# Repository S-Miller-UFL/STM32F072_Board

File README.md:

This is an STM32F072RBT6 based mcu board.

It contains the following features:
1. An ARM based STM32 microcontroller
2. An FT230 USB to UART transmitter that allows communication between the host computer and the MCU
3. A fully dedicated debug port. Labelled SWD.
4. 4 16 pin ports that are dedicated for communication with other boards. Such as SRAM, or FPGA's.

This design was made using KICAD. It's fully laid out, routed, and ready to be sent off for manufacturing.

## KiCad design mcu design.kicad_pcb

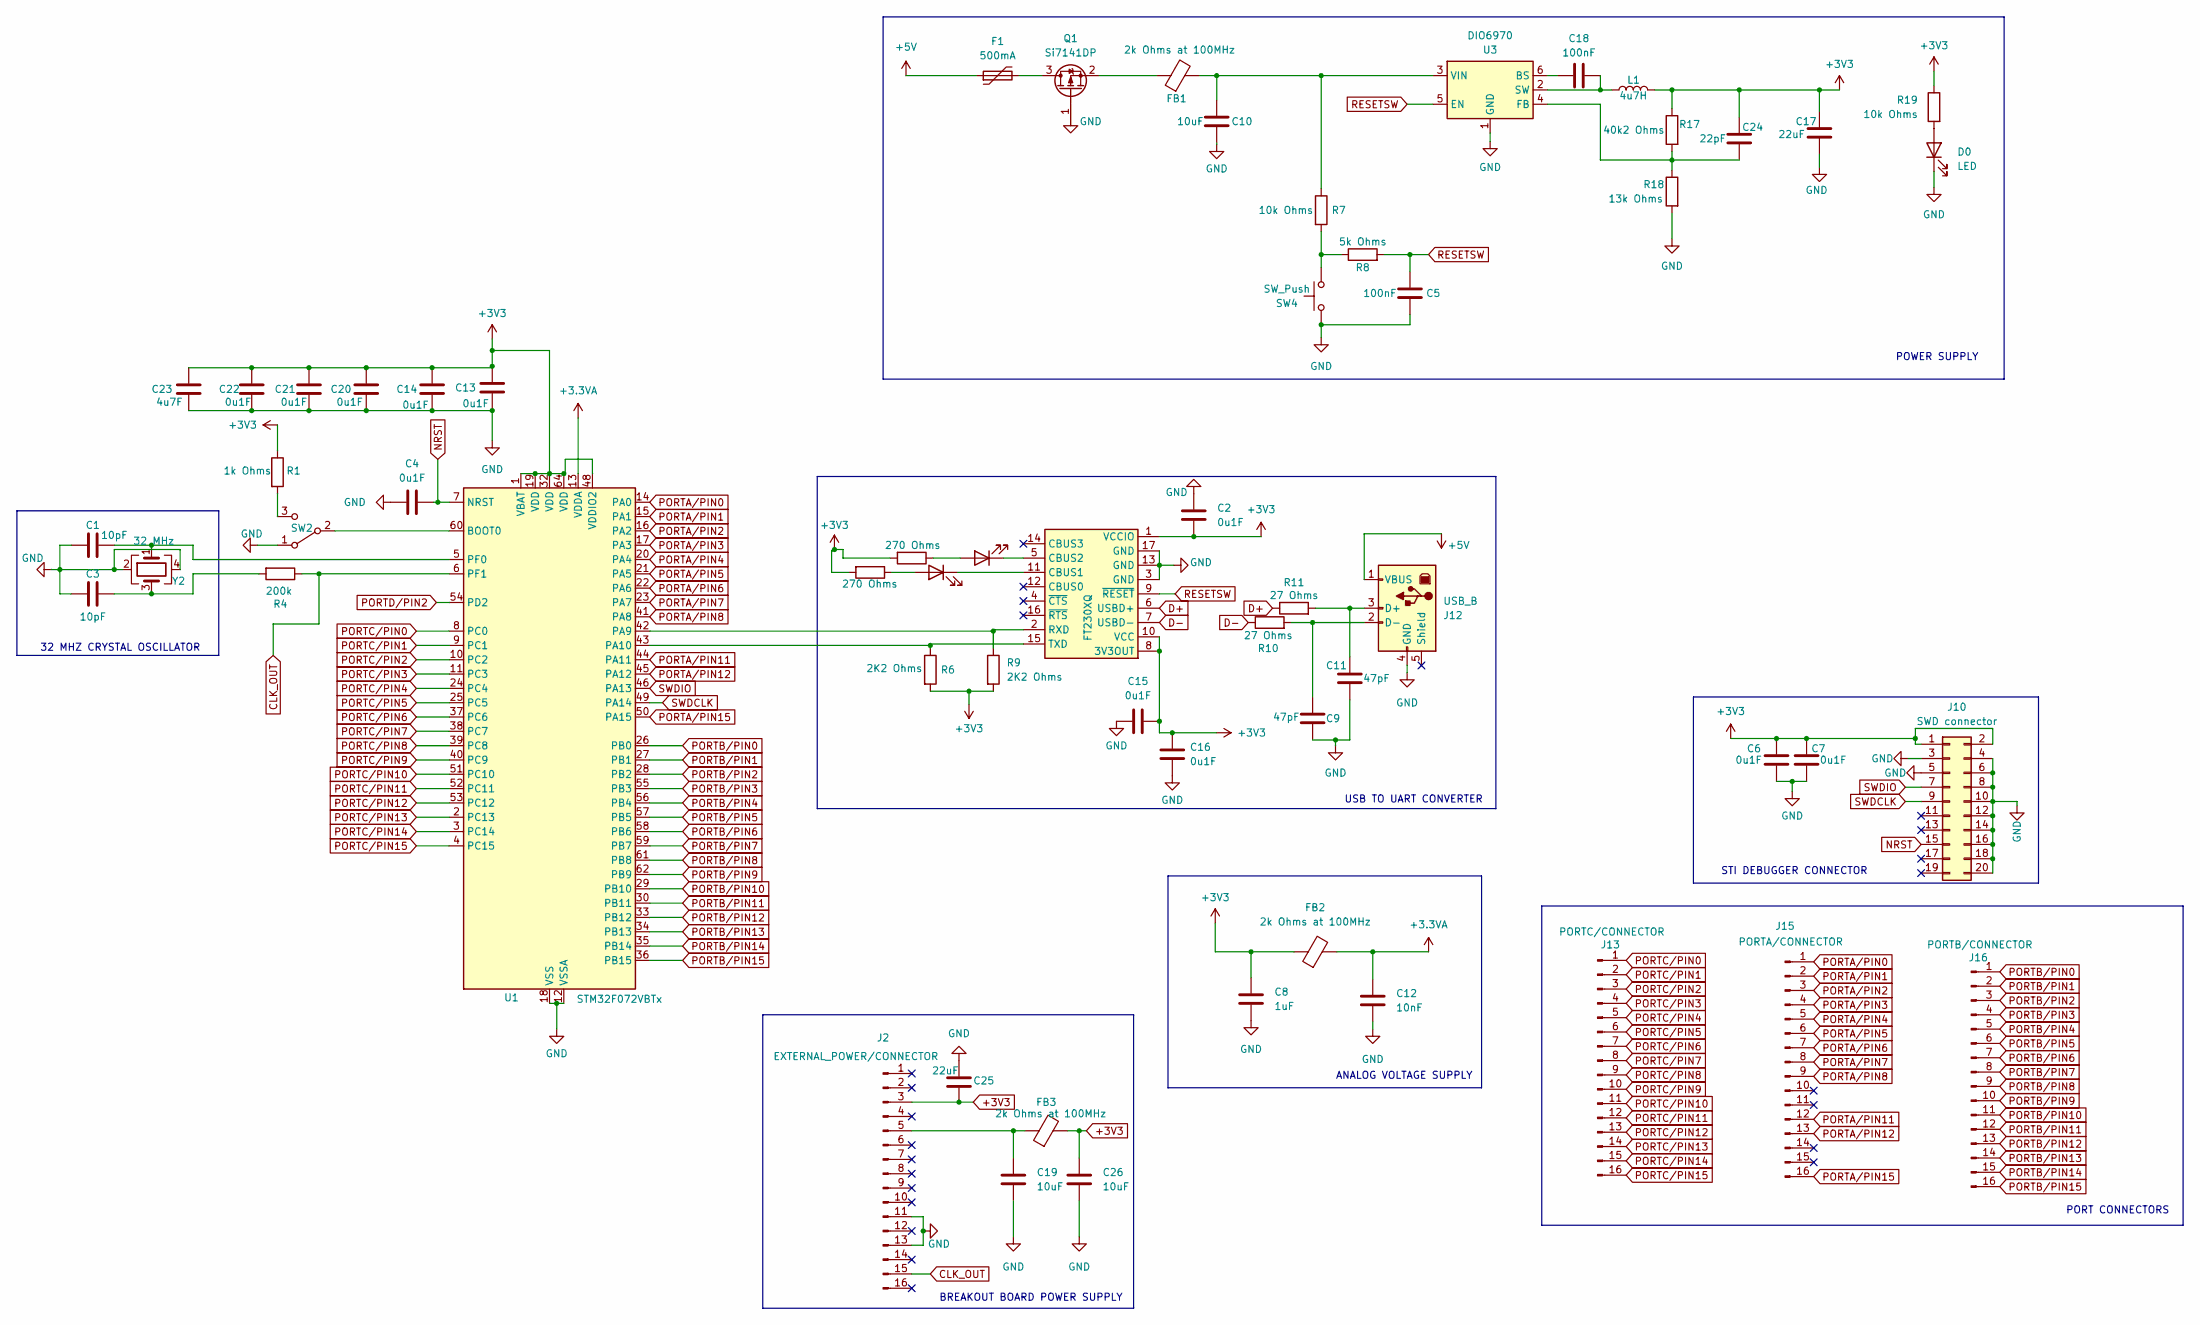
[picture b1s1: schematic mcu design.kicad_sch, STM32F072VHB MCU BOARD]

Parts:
C1, C3: 10pF; C_0402_1005Metric
C2, C4, C6, C7, C13, C14, C15, C16, C20, C21, C22: 0u1F; C_0402_1005Metric
C5, C18: 100nF; C_0402_1005Metric
C8: 1uF; C_0603_1608Metric
C9, C11: 47pF; C_0603_1608Metric
C10, C19, C26: 10uF; C_0603_1608Metric
C12: 10nF; C_0603_1608Metric
C17: 22uF; C_1206_3216Metric
C23: 4u7F; C_0402_1005Metric
C24: 22pF; C_0603_1608Metric
C25: 22uF; C_0402_1005Metric
D0, D1, D2: LED; LED_0603_1608Metric
F1: 500mA; Fuse_1206_3216Metric
FB1, FB2, FB3: 2k Ohms at 100MHz; L_0603_1608Metric
J2: EXTERNAL_POWER/CONNECTOR; PinHeader_1x16_P2.00mm_Vertical
J10: SWD connector; PinHeader_2x10_P2.00mm_Vertical
J12: USB_B; USB_B_Amphenol_MUSB-D511_Vertical_Rugged
J13: PORTC/CONNECTOR; PinHeader_1x16_P2.00mm_Vertical
J15: PORTA/CONNECTOR; PinHeader_1x16_P2.00mm_Vertical
J16: PORTB/CONNECTOR; PinHeader_1x16_P2.00mm_Vertical
L1: 4u7H; L_0805_2012Metric
Q1: Si7141DP; SOT-23
R1: 1k Ohms; R_0402_1005Metric
R2, R3: 270 Ohms; R_0402_1005Metric
R4: 200k; R_0402_1005Metric
R6, R9: 2K2 Ohms; R_0402_1005Metric
R7, R19: 10k Ohms; R_0402_1005Metric
R8: 5k Ohms; R_0402_1005Metric
R10, R11: 27 Ohms; R_0402_1005Metric
R17: 40k2 Ohms; R_0402_1005Metric
R18: 13k Ohms; R_0402_1005Metric
SW2: SW_CuK_JS202011CQN_DPDT_Straight
SW4: SW_Push; SW_Push_1P1T_NO_6x6mm_H9.5mm
U1: STM32F072VBTx; LQFP-64_10x10mm_P0.5mm
U2: FT230XQ; HTSSOP-16-1EP_4.4x5mm_P0.65mm_EP3.4x5mm
U3: DIO6970; SOT-23-6
Y2: 32 MHz; Crystal_SMD_2520-4Pin_2.5x2.0mm

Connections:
+3.3VA: C12.1, FB2.2, U1.13 (VDDA)
+3V3: C2.1, C6.1, C7.1, C8.1, C13.1, C14.1, C15.1, C16.1, C17.2, C20.1, C21.1, C22.1, C23.1, C24.2, C25.2, C26.1, FB2.1, FB3.2, J2.3, J10.1, J10.2, L1.2, R1.1, R2.2, R3.2, R6.2, R9.2, R17.1, R19.1, U1.1 (VBAT), U1.19 (VDD), U1.32 (VDD), U1.48 (VDDIO2), U1.64 (VDD), U2.1 (VCCIO), U2.8 (3V3OUT), U2.10 (VCC)
+5V: F1.1, J12.1 (VBUS)
CLK_OUT: J2.15, R4.1, U1.6 (PF1)
D+: R11.1, U2.6 (USBD+)
D-: R10.1, U2.7 (USBD-)
GND: C1.1, C2.2, C3.1, C4.1, C5.2, C6.2, C7.2, C8.2, C9.2, C10.2, C11.2, C12.2, C13.2, C14.2, C15.2, C16.2, C17.1, C19.2, C20.2, C21.2, C22.2, C23.2, C25.1, C26.2, D0.1 (K), J2.11, J2.13, J10.3, J10.4, J10.5, J10.6, J10.8, J10.10, J10.12, J10.14, J10.16, J10.18, J10.20, J12.4 (GND), Q1.1 (G), R18.2, SW2.1 (A), SW4.2, U1.12 (VSSA), U1.18 (VSS), U1.31 (VSS), U1.47 (VSS), U1.63 (VSS), U2.3 (GND), U2.13 (GND), U2.17 (GND), U3.1 (GND), Y2.2, Y2.4
NRST: C4.2, J10.15, U1.7 (NRST)
unnamed: C3.2, R4.2, Y2.3
unnamed: D0.2 (A), R19.2
unnamed: D1.2 (A), R2.1
unnamed: D1.1 (K), U2.11 (CBUS1)
unnamed: D2.2 (A), R3.1
unnamed: D2.1 (K), U2.5 (CBUS2)
unnamed: C19.1, FB3.1, J2.5
unnamed: C11.1, J12.3 (D+), R11.2
unnamed: C9.1, J12.2 (D-), R10.2
unnamed: F1.2, Q1.3 (D)
unnamed: FB1.1, Q1.2 (S)
unnamed: R7.2, R8.1, SW4.1
unnamed: SW2.2 (B), U1.60 (BOOT0)
unnamed: R1.2, SW2.3 (C)
unnamed: R9.1, U1.42 (PA9), U2.2 (RXD)
unnamed: R6.1, U1.43 (PA10), U2.15 (TXD)
unnamed: C1.2, U1.5 (PF0), Y2.1
unnamed: C18.1, U3.6 (BS)
unnamed: C24.1, R17.2, R18.1, U3.4 (FB)
unnamed: C18.2, L1.1, U3.2 (SW)
unnamed: C10.1, FB1.2, R7.1, U3.3 (VIN)
PORTA/PIN0: J15.1, U1.14 (PA0)
PORTA/PIN1: J15.2, U1.15 (PA1)
PORTA/PIN2: J15.3, U1.16 (PA2)
PORTA/PIN3: J15.4, U1.17 (PA3)
PORTA/PIN4: J15.5, U1.20 (PA4)
PORTA/PIN5: J15.6, U1.21 (PA5)
PORTA/PIN6: J15.7, U1.22 (PA6)
PORTA/PIN7: J15.8, U1.23 (PA7)
PORTA/PIN8: J15.9, U1.41 (PA8)
PORTA/PIN11: J15.12, U1.44 (PA11)
PORTA/PIN12: J15.13, U1.45 (PA12)
PORTA/PIN15: J15.16, U1.50 (PA15)
PORTB/PIN0: J16.1, U1.26 (PB0)
PORTB/PIN1: J16.2, U1.27 (PB1)
PORTB/PIN2: J16.3, U1.28 (PB2)
PORTB/PIN3: J16.4, U1.55 (PB3)
PORTB/PIN4: J16.5, U1.56 (PB4)
PORTB/PIN5: J16.6, U1.57 (PB5)
PORTB/PIN6: J16.7, U1.58 (PB6)
PORTB/PIN7: J16.8, U1.59 (PB7)
PORTB/PIN8: J16.9, U1.61 (PB8)
PORTB/PIN9: J16.10, U1.62 (PB9)
PORTB/PIN10: J16.11, U1.29 (PB10)
PORTB/PIN11: J16.12, U1.30 (PB11)
PORTB/PIN12: J16.13, U1.33 (PB12)
PORTB/PIN13: J16.14, U1.34 (PB13)
PORTB/PIN14: J16.15, U1.35 (PB14)
PORTB/PIN15: J16.16, U1.36 (PB15)
PORTC/PIN0: J13.1, U1.8 (PC0)
PORTC/PIN1: J13.2, U1.9 (PC1)
PORTC/PIN2: J13.3, U1.10 (PC2)
PORTC/PIN3: J13.4, U1.11 (PC3)
PORTC/PIN4: J13.5, U1.24 (PC4)
PORTC/PIN5: J13.6, U1.25 (PC5)
PORTC/PIN6: J13.7, U1.37 (PC6)
PORTC/PIN7: J13.8, U1.38 (PC7)
PORTC/PIN8: J13.9, U1.39 (PC8)
PORTC/PIN9: J13.10, U1.40 (PC9)
PORTC/PIN10: J13.11, U1.51 (PC10)
PORTC/PIN11: J13.12, U1.52 (PC11)
PORTC/PIN12: J13.13, U1.53 (PC12)
PORTC/PIN13: J13.14, U1.2 (PC13)
PORTC/PIN14: J13.15, U1.3 (PC14)
PORTC/PIN15: J13.16, U1.4 (PC15)
PORTD/PIN2: U1.54 (PD2)
RESETSW: C5.1, R8.2, U2.9 (~RESET), U3.5 (EN)
SWDCLK: J10.9, U1.49 (PA14)
SWDIO: J10.7, U1.46 (PA13)

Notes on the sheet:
POWER SUPPLY
32 MHZ CRYSTAL OSCILLATOR
PORT CONNECTORS
BREAKOUT BOARD POWER SUPPLY
USB TO UART CONVERTER
ANALOG VOLTAGE SUPPLY
STI DEBUGGER CONNECTOR

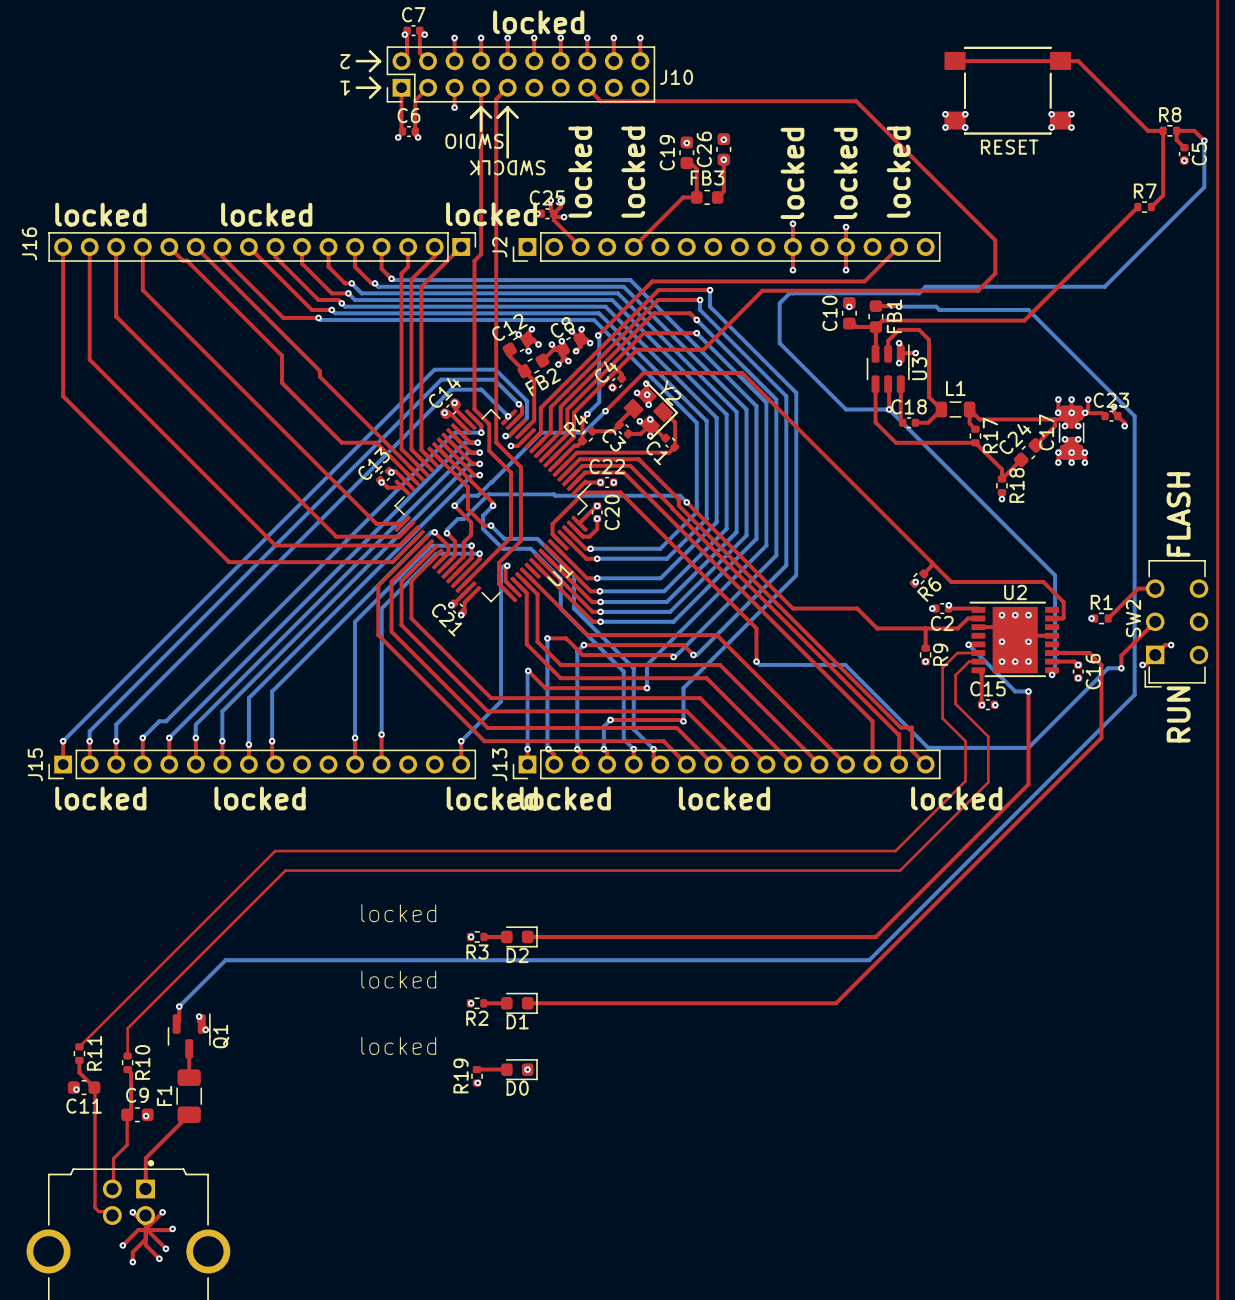
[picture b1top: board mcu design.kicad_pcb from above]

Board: 4 copper layers, 59 parts (0 on the bottom side), 75 nets.

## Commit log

2024-12-27 Created README.md
